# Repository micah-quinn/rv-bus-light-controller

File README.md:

# rv-bus-light-controller
A light controller built on commodity IoT hardware

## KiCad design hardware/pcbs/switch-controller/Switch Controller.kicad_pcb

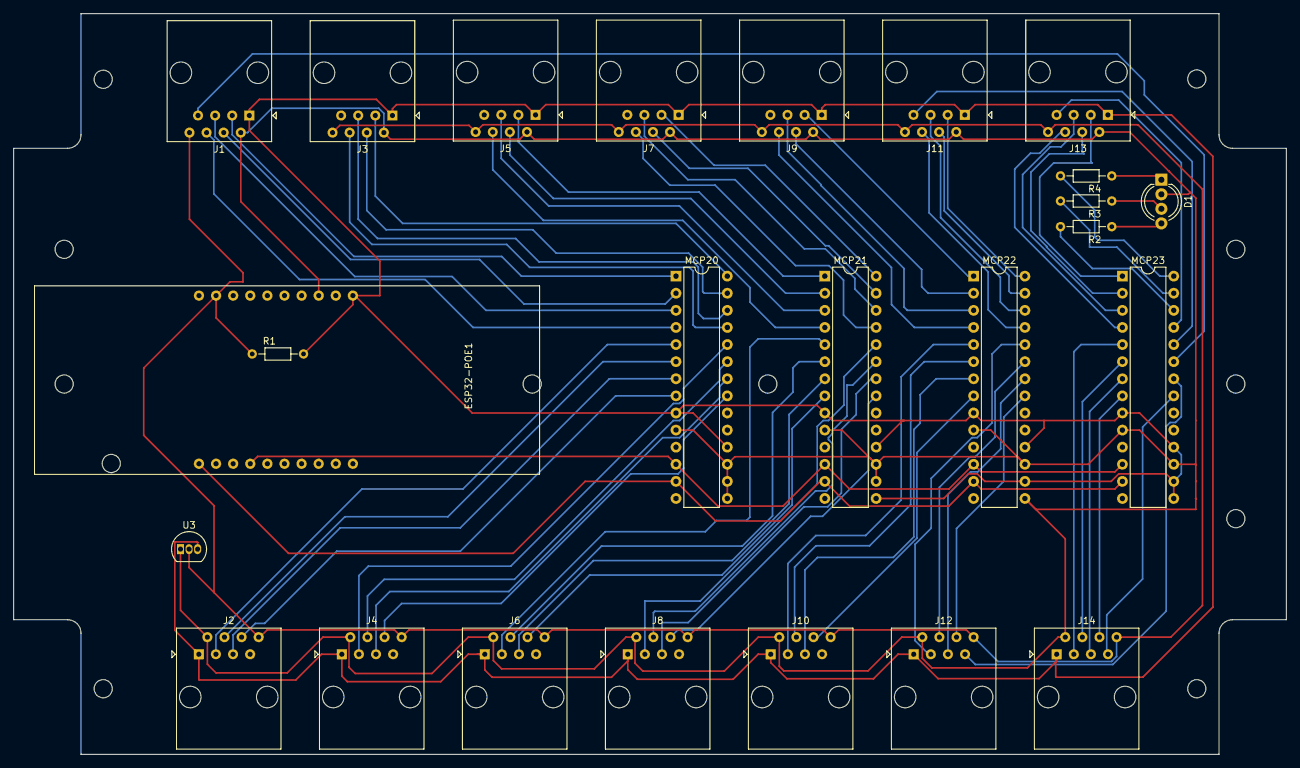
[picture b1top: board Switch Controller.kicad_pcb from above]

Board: 2 copper layers, 189.0 x 110.0 mm, 25 parts (0 on the bottom side), 72 nets.

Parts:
D1: LED_RCGB; LED_D5.0mm-4_RGB_Wide_Pins
ESP32-POE1: OlimexESP32-POE; Olimex_ESP32-POE-RevG
J1, J2, J3, J4, J5, J6, J7, J8, J9, J10, J11, J12, J13, J14: RJ45; RJ45_Amphenol_54602-x08_Horizontal
MCP20, MCP21, MCP22, MCP23: MCP23017_SP; DIP-28_W7.62mm
R1: 4.7K; R_Axial_DIN0204_L3.6mm_D1.6mm_P7.62mm_Horizontal
R2, R3: 470; R_Axial_DIN0204_L3.6mm_D1.6mm_P7.62mm_Horizontal
R4: 430; R_Axial_DIN0204_L3.6mm_D1.6mm_P7.62mm_Horizontal
U3: DS18B20; TO-92_Inline

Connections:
1-WIRE: ESP32-POE1.9, J1.8, J2.8, J3.8, J4.8, J5.8, J6.8, J7.8, J8.8, J9.8, J10.8, J11.8, J12.8, J13.8, J14.8, R1.1, U3.2
+5V: ESP32-POE1.1, J1.1, J2.1, J3.1, J4.1, J5.1, J6.1, J7.1, J8.1, J9.1, J10.1, J11.1, J12.1, J13.1, J14.1, MCP20.9, MCP20.18, MCP21.9, MCP21.15, MCP21.18, MCP22.9, MCP22.16, MCP22.18, MCP23.9, MCP23.15, MCP23.16, MCP23.18, R1.2, U3.3
GND: D1.2, ESP32-POE1.3, J1.2, J2.2, J3.2, J4.2, J5.2, J6.2, J7.2, J8.2, J9.2, J10.2, J11.2, J12.2, J13.2, J14.2, MCP20.10, MCP20.15, MCP20.16, MCP20.17, MCP21.10, MCP21.16, MCP21.17, MCP22.10, MCP22.15, MCP22.17, MCP23.10, MCP23.17, U3.1
I2C_SCL: ESP32-POE1.17, MCP20.12, MCP21.12, MCP22.12, MCP23.12
I2C_SDA: ESP32-POE1.20, MCP20.13, MCP21.13, MCP22.13, MCP23.13
unnamed: D1.1, R4.1
unnamed: D1.3, R3.1
unnamed: D1.4, R2.1
unnamed: J1.3, MCP20.1
unnamed: J1.4, MCP20.2
unnamed: J1.5, MCP20.3
unnamed: J1.6, MCP20.4
unnamed: J1.7, MCP23.23
unnamed: J2.3, MCP20.5
unnamed: J2.4, MCP20.6
unnamed: J2.5, MCP20.7
unnamed: J2.6, MCP20.8
unnamed: J3.3, MCP20.28
unnamed: J3.4, MCP20.27
unnamed: J3.5, MCP20.26
unnamed: J3.6, MCP20.25
unnamed: J4.3, MCP20.24
unnamed: J4.4, MCP20.23
unnamed: J4.5, MCP20.22
unnamed: J4.6, MCP20.21
unnamed: J5.3, MCP21.1
unnamed: J5.4, MCP21.2
unnamed: J5.5, MCP21.3
unnamed: J5.6, MCP21.4
unnamed: J6.3, MCP21.5
unnamed: J6.4, MCP21.6
unnamed: J6.5, MCP21.7
unnamed: J6.6, MCP21.8
unnamed: J7.3, MCP21.28
unnamed: J7.4, MCP21.27
unnamed: J7.5, MCP21.26
unnamed: J7.6, MCP21.25
unnamed: J8.3, MCP21.24
unnamed: J8.4, MCP21.23
unnamed: J8.5, MCP21.22
unnamed: J8.6, MCP21.21
unnamed: J9.3, MCP22.1
unnamed: J9.4, MCP22.2
unnamed: J9.5, MCP22.3
unnamed: J9.6, MCP22.4
unnamed: J10.3, MCP22.5
unnamed: J10.4, MCP22.6
unnamed: J10.5, MCP22.7
unnamed: J10.6, MCP22.8
unnamed: J11.3, MCP22.28
unnamed: J11.4, MCP22.27
unnamed: J11.5, MCP22.26
unnamed: J11.6, MCP22.25
unnamed: J11.7, MCP23.24
unnamed: J12.3, MCP22.24
unnamed: J12.4, MCP22.23
unnamed: J12.5, MCP22.22
unnamed: J12.6, MCP22.21
unnamed: J12.7, MCP23.22
unnamed: J13.3, MCP23.1
unnamed: J13.4, MCP23.2
unnamed: J13.5, MCP23.3
unnamed: J13.6, MCP23.4
unnamed: J13.7, MCP23.25
unnamed: J14.3, MCP23.5
unnamed: J14.4, MCP23.6
unnamed: J14.5, MCP23.7
unnamed: J14.6, MCP23.8
unnamed: J14.7, MCP23.21
unnamed: MCP23.26, R2.2
unnamed: MCP23.27, R3.2
unnamed: MCP23.28, R4.2

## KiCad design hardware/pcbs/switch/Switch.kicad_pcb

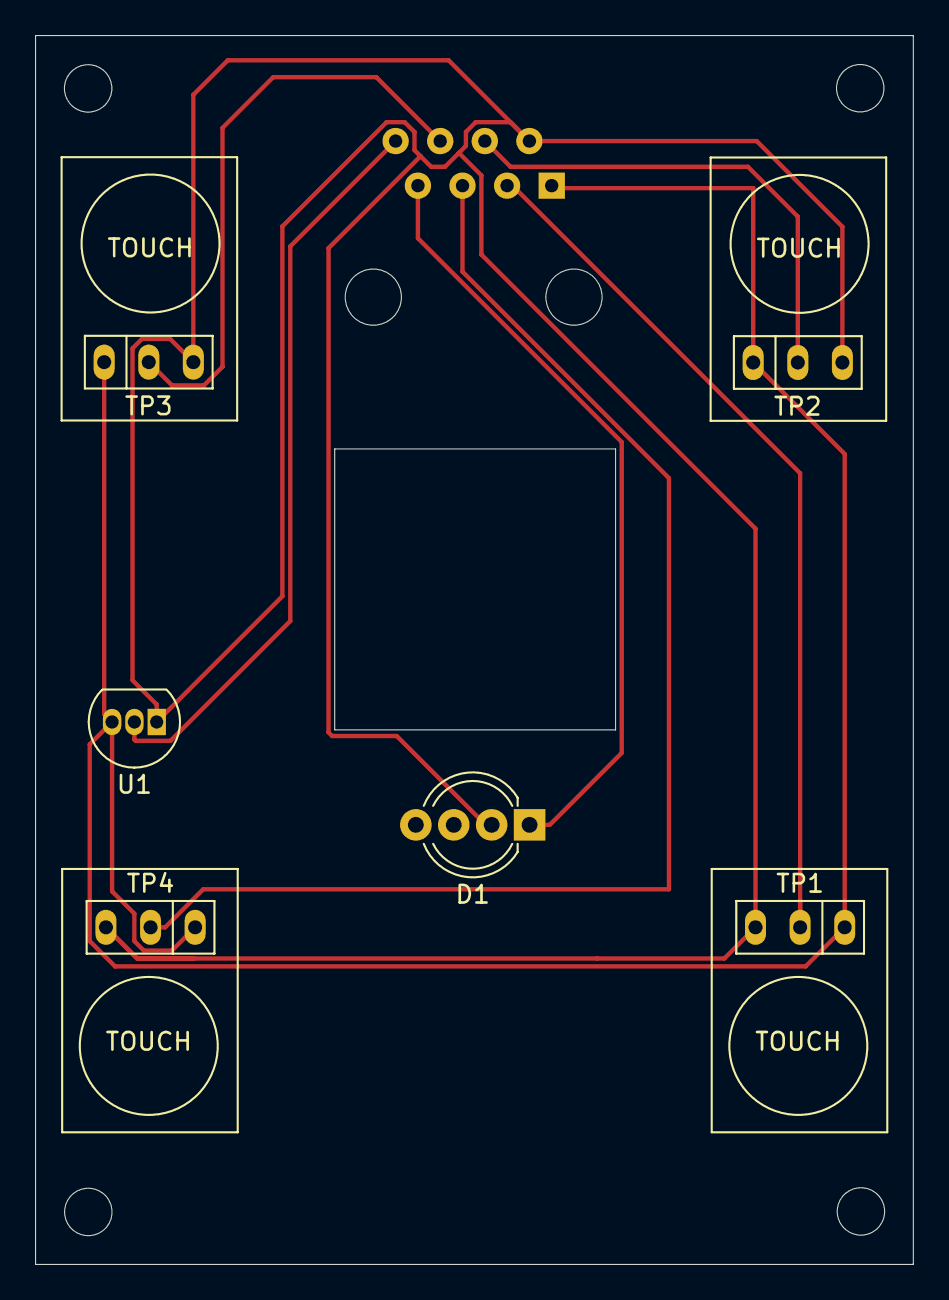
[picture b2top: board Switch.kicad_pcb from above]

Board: 2 copper layers, 50.0 x 70.0 mm, 7 parts (1 on the bottom side), 8 nets.

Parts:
D1: LED_RCGB; LED_D5.0mm-4_RGB_Wide_Pins
J1: RJ45; RJ45_Amphenol_54602-x08_Horizontal
TP1, TP2, TP3, TP4: TP233_Touch_Pad; TTP23_Touch_Pad
U1: DS18B20; TO-92_Inline

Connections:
GND: D1.2, J1.2, TP1.3, TP2.3, TP3.3, TP4.3, U1.1
unnamed: D1.1, J1.7
unnamed: J1.3, TP1.2
unnamed: J1.4, TP2.2
unnamed: J1.5, TP4.2
unnamed: J1.6, TP3.2
unnamed: J1.8, U1.2
VCC: J1.1, TP1.1, TP2.1, TP3.1, TP4.1, U1.3

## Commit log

2022-02-15 Initial check-in of files.
2022-07-11 Updating
2022-07-11 Adding dimmer control
2022-07-11 Changing state/power levels to global context for use in sub-flows
